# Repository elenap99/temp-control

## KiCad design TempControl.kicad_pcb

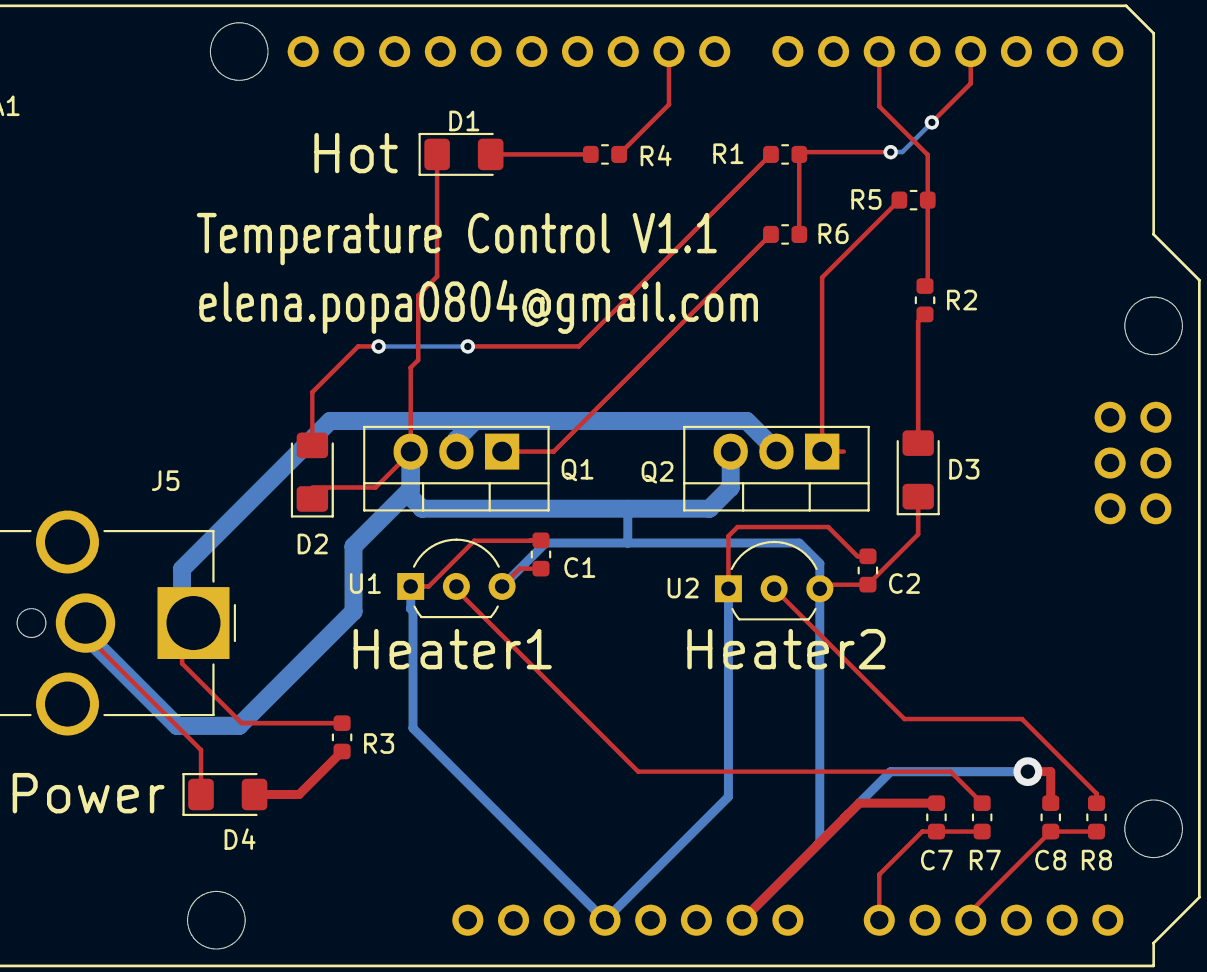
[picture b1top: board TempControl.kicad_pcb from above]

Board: 2 copper layers, 22 parts (0 on the bottom side), 16 nets.

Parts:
C1, C2, C7, C8: C; C_0603_1608Metric
D1, D2, D3, D4: LED; D_1206_3216Metric_Pad1.42x1.75mm_HandSolder
J5: Barrel_Jack_Switch; BarrelJack_CUI_PJ-063AH_Horizontal_CircularHoles
Q1, Q2: TIP41C; TO-220-3_Vertical
R1, R2, R3, R4, R5, R6, R7, R8: R; R_0603_1608Metric
U1, U2: TMP36GT9Z; TO-92L_Inline_Wide
XA1: Arduino_Uno_Shield

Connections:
GND: C1.2, C2.2, C7.1, C8.2, D1.1, D2.1, D3.1, D4.1, J5.2, Q1.3, Q2.3, U1.3, U2.3, XA1.GND3
unnamed: C1.1, C2.1, U1.1, U2.1, XA1.3V3
unnamed: C7.2, R7.1, XA1.A0
unnamed: C8.1, R8.2, XA1.A2
unnamed: D1.2, R4.1
unnamed: D2.2, R1.1
unnamed: D3.2, R2.1
unnamed: D4.2, R3.1
unnamed: Q1.1, R6.1
unnamed: Q2.1, R5.2
unnamed: R1.2, R6.2, XA1.D3
unnamed: R2.2, R5.1, XA1.D5
unnamed: R4.2, XA1.D9
unnamed: R7.2, U1.2
unnamed: R8.1, U2.2
Vcc: J5.1, Q1.2, Q2.2, R3.2
